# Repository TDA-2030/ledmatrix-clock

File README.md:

# LED Matrix Clock

A LED matrix clock controlled by [ESP32](https://www.espressif.com/en/products/socs/esp32) for a room. This clock includes a 32x64 Red and Green led matrix panel. 

## Feature

- [x] Connect Internet with Wi-Fi
- [x] Auto update time 
- [x] Web OTA
- [ ] Time report on the hour
- [x] Automatically update weather information 
- [x] Automatically adjust display brightness 
- [ ] The lunar calendar and solar terms can be displayed
- [ ] Play music with Bluetooth
- [ ] Display any text from configuration webpage write

## Information displayed

- Time
- Date
- Week
- Temperature
- Humidity
- Lunar calendar
- Recent weather

## Demonstration

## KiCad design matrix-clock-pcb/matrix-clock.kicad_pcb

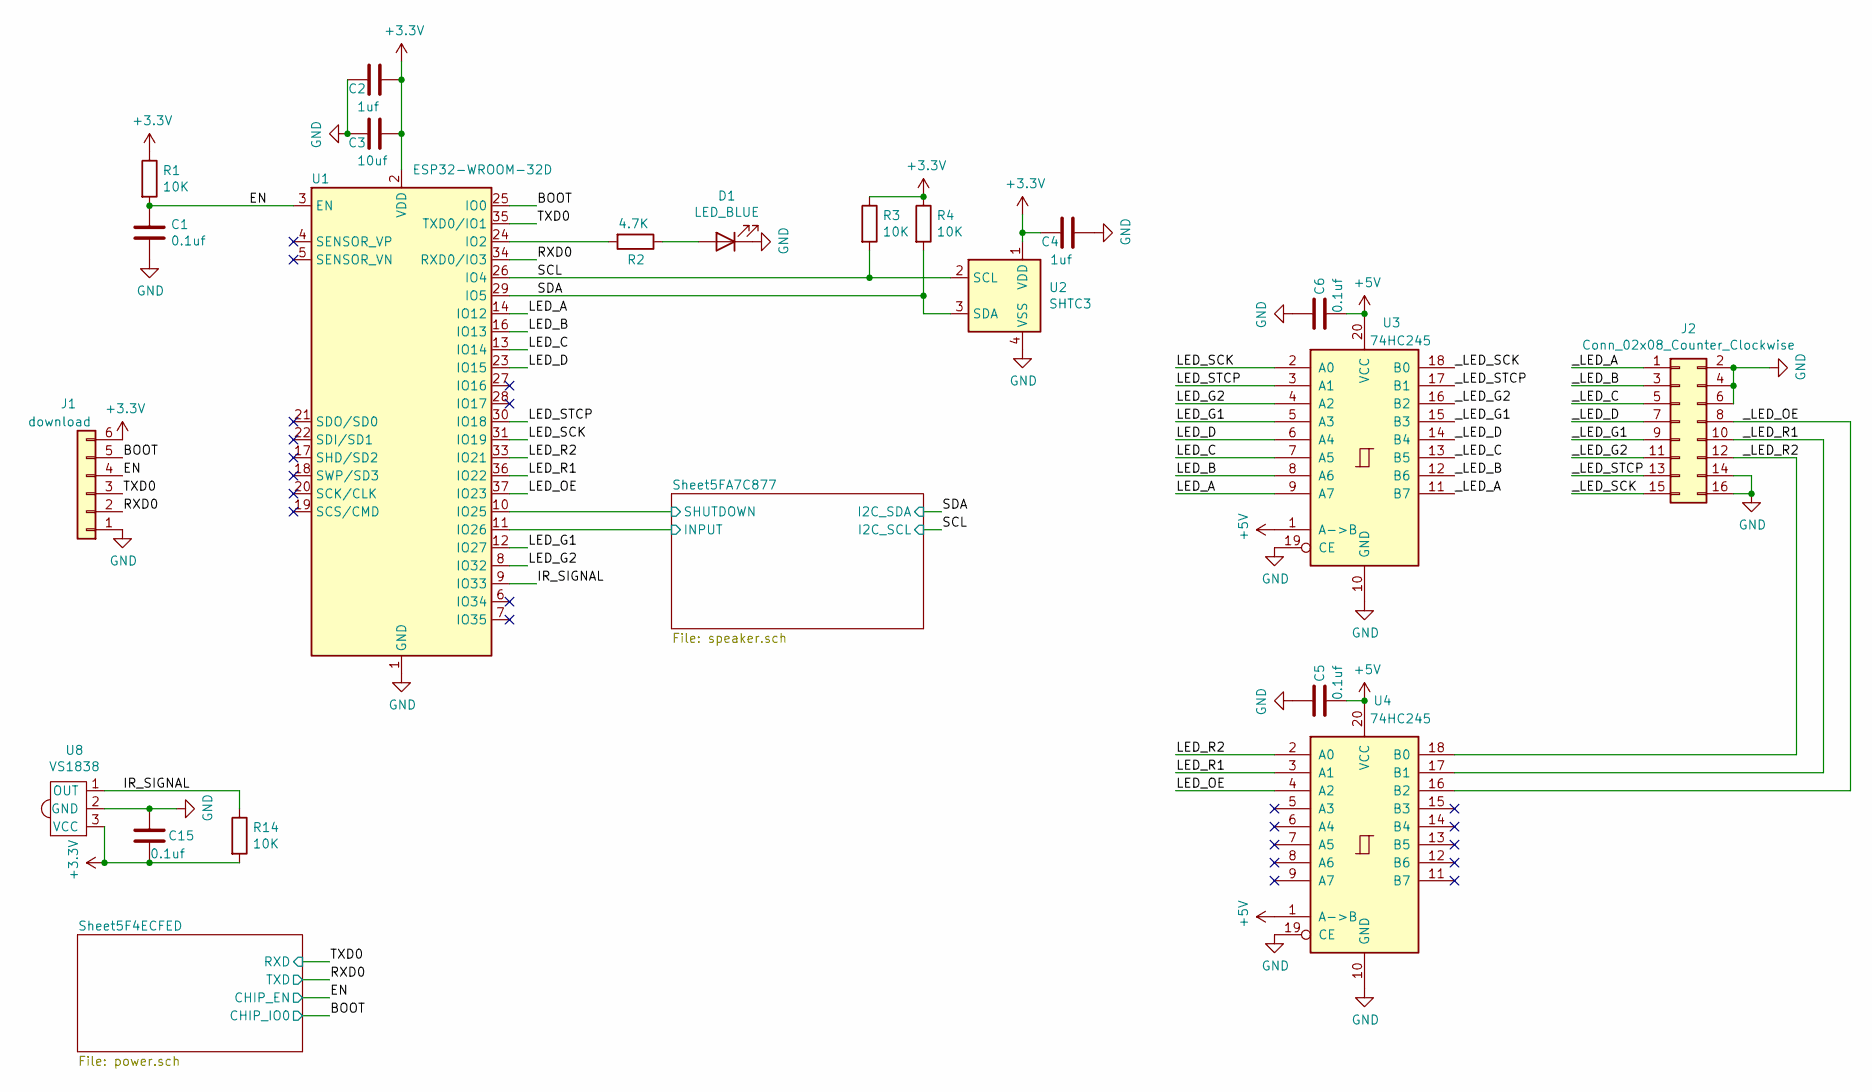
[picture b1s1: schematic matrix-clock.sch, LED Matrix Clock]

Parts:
C1, C5, C6, C15: 0.1uf; C_0402_1005Metric
C2, C4: 1uf; C_0603_1608Metric
C3: 10uf; C_0805_2012Metric
D1: LED_BLUE; LED_0603_1608Metric
J1: download; PinHeader_1x06_P2.54mm_Vertical
J2: Conn_02x08_Counter_Clockwise; PinHeader_2x08_P2.54mm_Vertical
R1, R3, R4, R14: 10K; R_0402_1005Metric
R2: 4.7K; R_0402_1005Metric
U1: ESP32-WROOM-32D; ESP32-WROOM-32
U2: SHTC3; Sensirion_DFN-4-1EP_2x2mm_P1mm_EP0.7x1.6mm
U3, U4: 74HC245; TSSOP-20_4.4x6.5mm_P0.65mm
U8: VS1838; Infrared_Receiver_module

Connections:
+3V3: C2.1, C3.1, C4.2, C15.2, J1.6, R1.1, R3.1, R4.1, R14.2, U1.2 (VDD), U2.1 (VDD), U8.3 (VCC); also elsewhere on the board
+5V: C5.2, C6.2, U3.1 (A->B), U3.20 (VCC), U4.1 (A->B), U4.20 (VCC); also elsewhere on the board
/BOOT: J1.5, U1.25 (IO0); also elsewhere on the board
/EN: C1.1, J1.4, R1.2, U1.3 (EN); also elsewhere on the board
/IR_SIGNAL: R14.1, U1.9 (IO33), U8.1 (OUT)
/LED_A: U1.14 (IO12), U3.9 (A7)
/LED_B: U1.16 (IO13), U3.8 (A6)
/LED_C: U1.13 (IO14), U3.7 (A5)
/LED_D: U1.23 (IO15), U3.6 (A4)
/LED_G1: U1.12 (IO27), U3.5 (A3)
/LED_G2: U1.8 (IO32), U3.4 (A2)
/LED_OE: U1.37 (IO23), U4.4 (A2)
/LED_R1: U1.36 (IO22), U4.3 (A1)
/LED_R2: U1.33 (IO21), U4.2 (A0)
/LED_SCK: U1.31 (IO19), U3.2 (A0)
/LED_STCP: U1.30 (IO18), U3.3 (A1)
/RXD0: J1.2, U1.34 (RXD0/IO3); also elsewhere on the board
/SCL: R3.2, U1.26 (IO4), U2.2 (SCL); also elsewhere on the board
/SDA: R4.2, U1.29 (IO5), U2.3 (SDA); also elsewhere on the board
/Sheet5FA7C877/INPUT: U1.11 (IO26); also elsewhere on the board
/Sheet5FA7C877/SHUTDOWN: U1.10 (IO25); also elsewhere on the board
/TXD0: J1.3, U1.35 (TXD0/IO1); also elsewhere on the board
/_LED_A: J2.1, U3.11 (B7)
/_LED_B: J2.3, U3.12 (B6)
/_LED_C: J2.5, U3.13 (B5)
/_LED_D: J2.7, U3.14 (B4)
/_LED_G1: J2.9, U3.15 (B3)
/_LED_G2: J2.11, U3.16 (B2)
/_LED_OE: J2.8, U4.16 (B2)
/_LED_R1: J2.10, U4.17 (B1)
/_LED_R2: J2.12, U4.18 (B0)
/_LED_SCK: J2.15, U3.18 (B0)
/_LED_STCP: J2.13, U3.17 (B1)
GND: C1.2, C2.2, C3.2, C4.1, C5.1, C6.1, C15.1, D1.1 (K), J1.1, J2.2, J2.4, J2.6, J2.14, J2.16, U1.1 (GND), U1.15 (GND), U1.38 (GND), U1.39 (GND), U2.4 (VSS), U3.10 (GND), U3.19 (CE), U4.10 (GND), U4.19 (CE), U8.2 (GND); also elsewhere on the board
unnamed: D1.2 (A), R2.1
unnamed: R2.2, U1.24 (IO2)

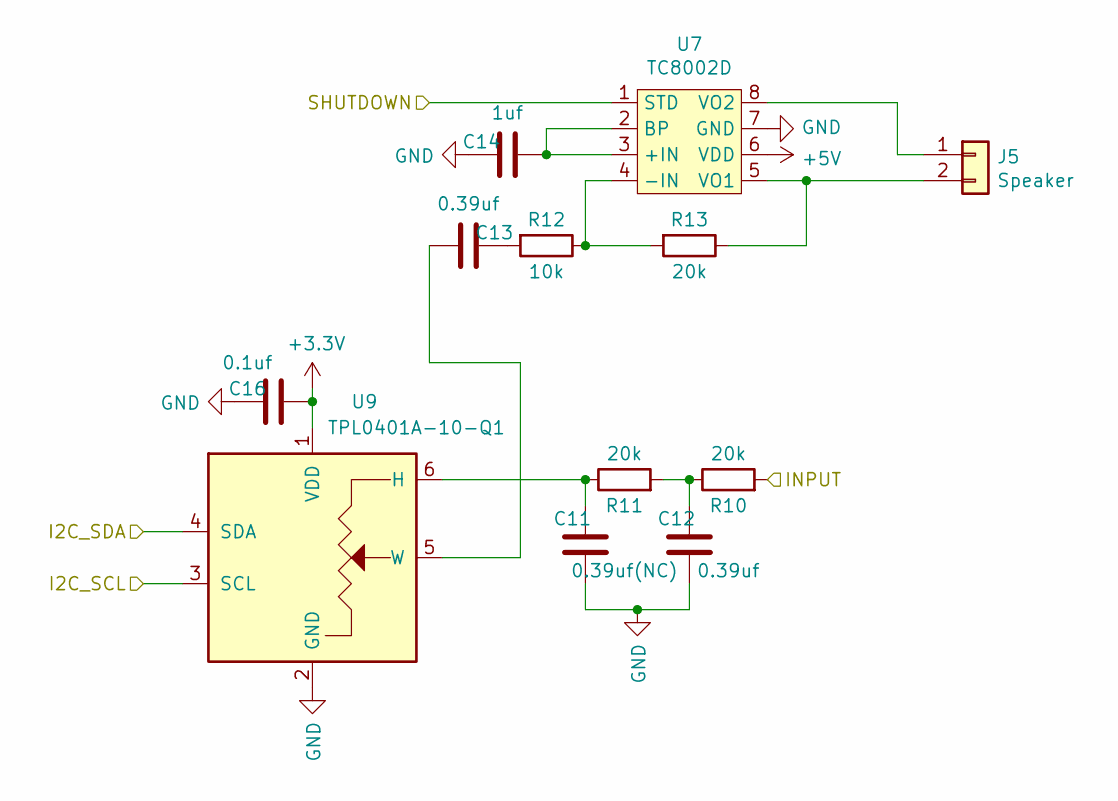
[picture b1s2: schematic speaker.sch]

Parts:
C11: 0.39uf(NC); C_0402_1005Metric
C12, C13: 0.39uf; C_0402_1005Metric
C14: 1uf; C_0402_1005Metric
C16: 0.1uf; C_0402_1005Metric
J5: Speaker; PinHeader_1x02_P2.54mm_Vertical
R10, R11, R13: 20k; R_0402_1005Metric
R12: 10k; R_0402_1005Metric
U7: TC8002D; SOIC-8_3.9x4.9mm_P1.27mm
U9: TPL0401A-10-Q1; Texas_R-PDSO-G6

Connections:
+3V3: C16.1, U9.1 (VDD); also elsewhere on the board
+5V: U7.6 (VDD); also elsewhere on the board
/SCL: U9.3 (SCL); also elsewhere on the board
/SDA: U9.4 (SDA); also elsewhere on the board
/Sheet5FA7C877/INPUT: R10.2; also elsewhere on the board
/Sheet5FA7C877/SHUTDOWN: U7.1 (STD); also elsewhere on the board
GND: C11.1, C12.1, C14.2, C16.2, U7.7 (GND), U9.2 (GND); also elsewhere on the board
unnamed: C11.2, R11.1, U9.6 (H)
unnamed: C12.2, R10.1, R11.2
unnamed: C13.1, R12.2
unnamed: C13.2, U9.5 (W)
unnamed: C14.1, U7.2 (BP), U7.3 (+IN)
unnamed: J5.1, U7.8 (VO2)
unnamed: J5.2, R13.1, U7.5 (VO1)
unnamed: R12.1, R13.2, U7.4 (-IN)

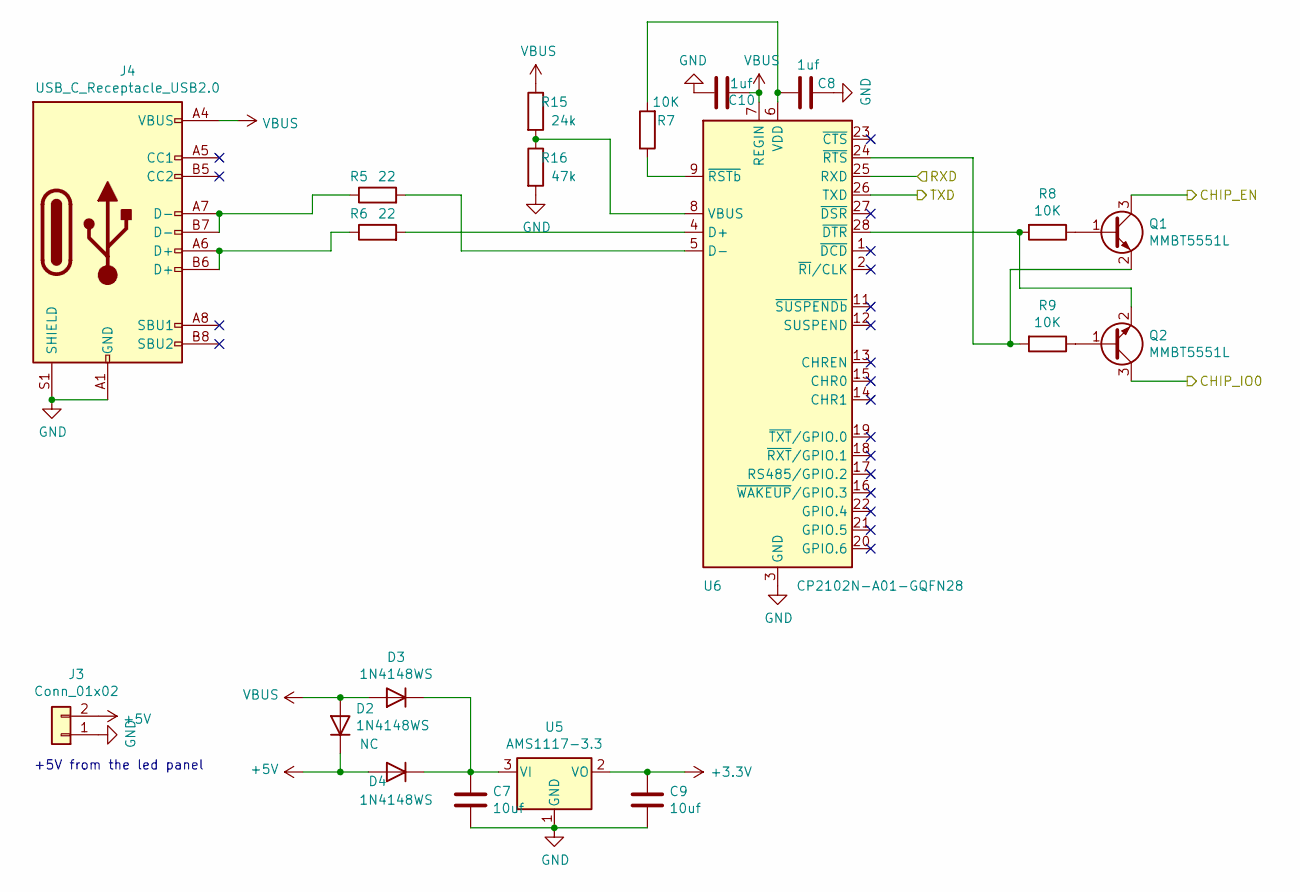
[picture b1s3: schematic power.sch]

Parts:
C7, C9: 10uf; C_0805_2012Metric
C8, C10: 1uf; C_0402_1005Metric
D2, D3, D4: 1N4148WS; D_SOD-323
J3: Conn_01x02; PinHeader_1x02_P2.54mm_Vertical
J4: USB_C_Receptacle_USB2.0; USB_C_Receptacle_HRO_TYPE-C-31-M-12
Q1, Q2: MMBT5551L; SOT-23
R5, R6: 22; R_0402_1005Metric
R7, R8, R9: 10K; R_0402_1005Metric
R15: 24k; R_0402_1005Metric
R16: 47k; R_0402_1005Metric
U5: AMS1117-3.3; SOT-223-3_TabPin2
U6: CP2102N-A01-GQFN28; QFN-28-1EP_5x5mm_P0.5mm_EP3.35x3.35mm

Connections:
+3V3: C9.1, U5.2 (VO); also elsewhere on the board
+5V: D2.1 (K), D4.2 (A), J3.2; also elsewhere on the board
/BOOT: Q2.3 (C); also elsewhere on the board
/EN: Q1.3 (C); also elsewhere on the board
/RXD0: U6.26 (TXD); also elsewhere on the board
/TXD0: U6.25 (RXD); also elsewhere on the board
GND: C7.2, C8.1, C9.2, C10.2, J3.1, J4.A1 (GND), J4.A12 (GND), J4.B1 (GND), J4.B12 (GND), J4.S1 (SHIELD), R16.2, U5.1 (GND), U6.3 (GND), U6.29 (GND); also elsewhere on the board
unnamed: C7.1, D3.1 (K), D4.1 (K), U5.3 (VI)
unnamed: C8.2, R7.2, U6.6 (VDD)
unnamed: J4.A6 (D+), J4.B6 (D+), R6.1
unnamed: J4.A7 (D-), J4.B7 (D-), R5.1
unnamed: Q1.1 (B), R8.1
unnamed: Q1.2 (E), R9.2, U6.24 (~RTS)
unnamed: Q2.1 (B), R9.1
unnamed: Q2.2 (E), R8.2, U6.28 (~DTR)
unnamed: R5.2, U6.5 (D-)
unnamed: R6.2, U6.4 (D+)
unnamed: R7.1, U6.9 (~RSTb)
unnamed: R15.2, R16.1, U6.8 (VBUS)
VBUS: C10.1, D2.2 (A), D3.2 (A), J4.A4 (VBUS), J4.A9 (VBUS), J4.B4 (VBUS), J4.B9 (VBUS), R15.1, U6.7 (REGIN)

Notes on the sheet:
+5V from the led panel

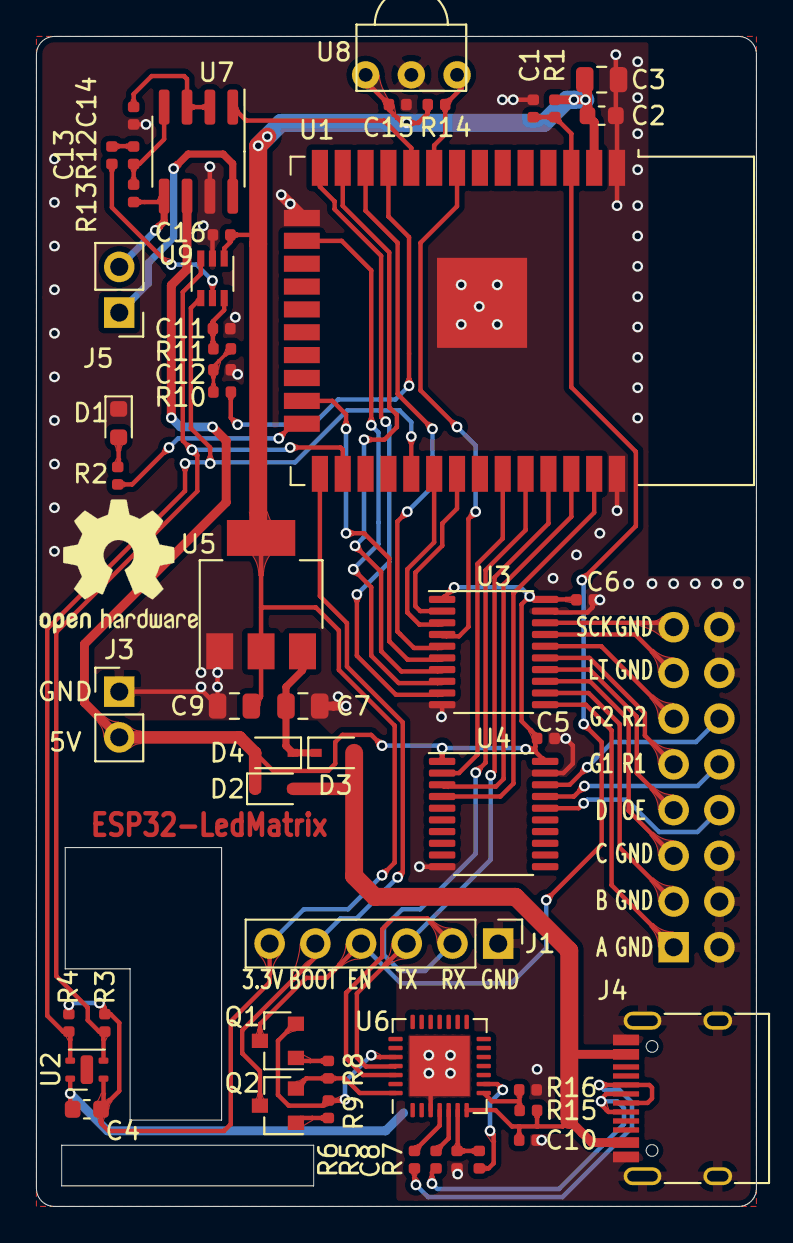
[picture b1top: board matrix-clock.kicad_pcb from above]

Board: 2 copper layers, 40.0 x 65.0 mm, 52 parts (1 on the bottom side), 57 nets.

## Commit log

2020-10-09 add replace smartconfig with webconfig
2020-10-13 fix(weather): add cjson parse
2020-10-14 fix(weeather): add json check
2020-10-16 fix(weather): add cjson parse function
2020-10-16 fix(main): add lunar calendar
2020-10-16 fix(webpage_config): reduce compile warning
2020-11-07 fix(ledmatrix): modify gpio
2020-11-07 feat: add calendar component
2020-11-07 fix(main): add spiffs image and move sntp code
2020-11-07 WIP: add some components
2020-11-08 fix: add mp3_player function
2020-11-09 feat(pcb): add pcb files
2020-11-13 refactor: organize files structure
2020-11-13 pcb: update pcb files
2020-11-14 feat: add SHTC3 sensor and chinese display
2020-11-15 fix(lcd_paint): modify font struct to fit gbk code
2020-11-15 test(main): add gbk test
2020-11-15 fix(main): restore spiffs image flash in project
2020-11-16 fix(shtcx): fix read error temporary
2020-11-17 fix(shtcx): modify driver to official example
2020-11-22 pcb: update pcb to v1.1
2020-11-22 doc: add shtc3 datasheet
2020-11-27 chore: rename component lcd_paint to paint
2020-12-02 refactor(audio): delete dac_audio and modify helix structure
2020-12-02 feat(a2dp): add bt audio play
2020-12-06 refactor(sntp): modify sntp
2020-12-06 feat(paint): add roll text function
2020-12-06 fix(led_matrix): add brightness gamma calibration
2020-12-06 fix(main): add board.c
2020-12-06 docs: update README.md
2020-12-06 fix(led_matrix): modify timer intervalue to 500us
2020-12-06 feat(file_serve): add mdns
2020-12-06 chore(spiffs_image): delete mp3 audio file
2020-12-06 fix(paint): add some fonts, fix crash issue when delete roll text
2020-12-06 feat(main): add restore function
2020-12-06 fix(shtcx): fix read error by increase delay time
2020-12-06 fix(calendar): fix calendar_get_lunar_str return unsuitable string issue
2020-12-15 docs: add badge
2020-12-27 fix(paint): modify roll text and show clock
2020-12-27 fix(weather): add api to get string
2020-12-27 fix(calendar): fix issue when at last jieqi
2020-12-27 fix(main): add weather and lunar display
2021-02-08 feat(component): add esp32-fft
2021-03-07 add panel drawing
2021-03-07 fix(sntp): modify ntp server and remove some redundant code
2021-03-07 fix(shtcx): add an independent i2c_buc component
2021-03-07 fix(led_matrix): remove unused font
2021-03-07 feat(ssd1306): add ssd1306 as new display device
2021-03-07 fix(pcb): modify cp2102 IO voltage to 3.3v; add ir receiver
2021-03-08 fix(pcb): update pcb layout
2021-03-10 chore: clean led_matrix
2021-03-10 fix(ssd1306): improve efficiency of refresh function
2021-03-11 feat(oled): add sh1106
2021-03-20 pcb: add ibom
2021-05-03 feat: add tpl0401 driver for regulate volume
2021-07-25 feat: add wetb ota
2021-07-25 feat: add github action
2021-09-19 fix(sntp): add ntp some server
2021-12-04 add fft
2021-12-05 add screen
2021-12-06 add mic
2022-04-06 add font display
2025-02-11 add LVGL
